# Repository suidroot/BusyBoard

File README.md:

# BusyBoard

The Busy board is a board designed for experimetning with various Microcontroller Dev boards. It is there to give you LEDs to make blink, various, buttons, switches and knobs to learn and test code against. The choice in components is based around what parts I have on hand and what is easily available in most beginers kits.

_Currently it has the following features_
* 4x LEDs
* 4x push buttons
* 8x DIP switches
* 1x Rotary Encorder
* 1x variable potentiometer
* Optional Pull up resistors (enabled by switch)
* Small power distribution array of Pins

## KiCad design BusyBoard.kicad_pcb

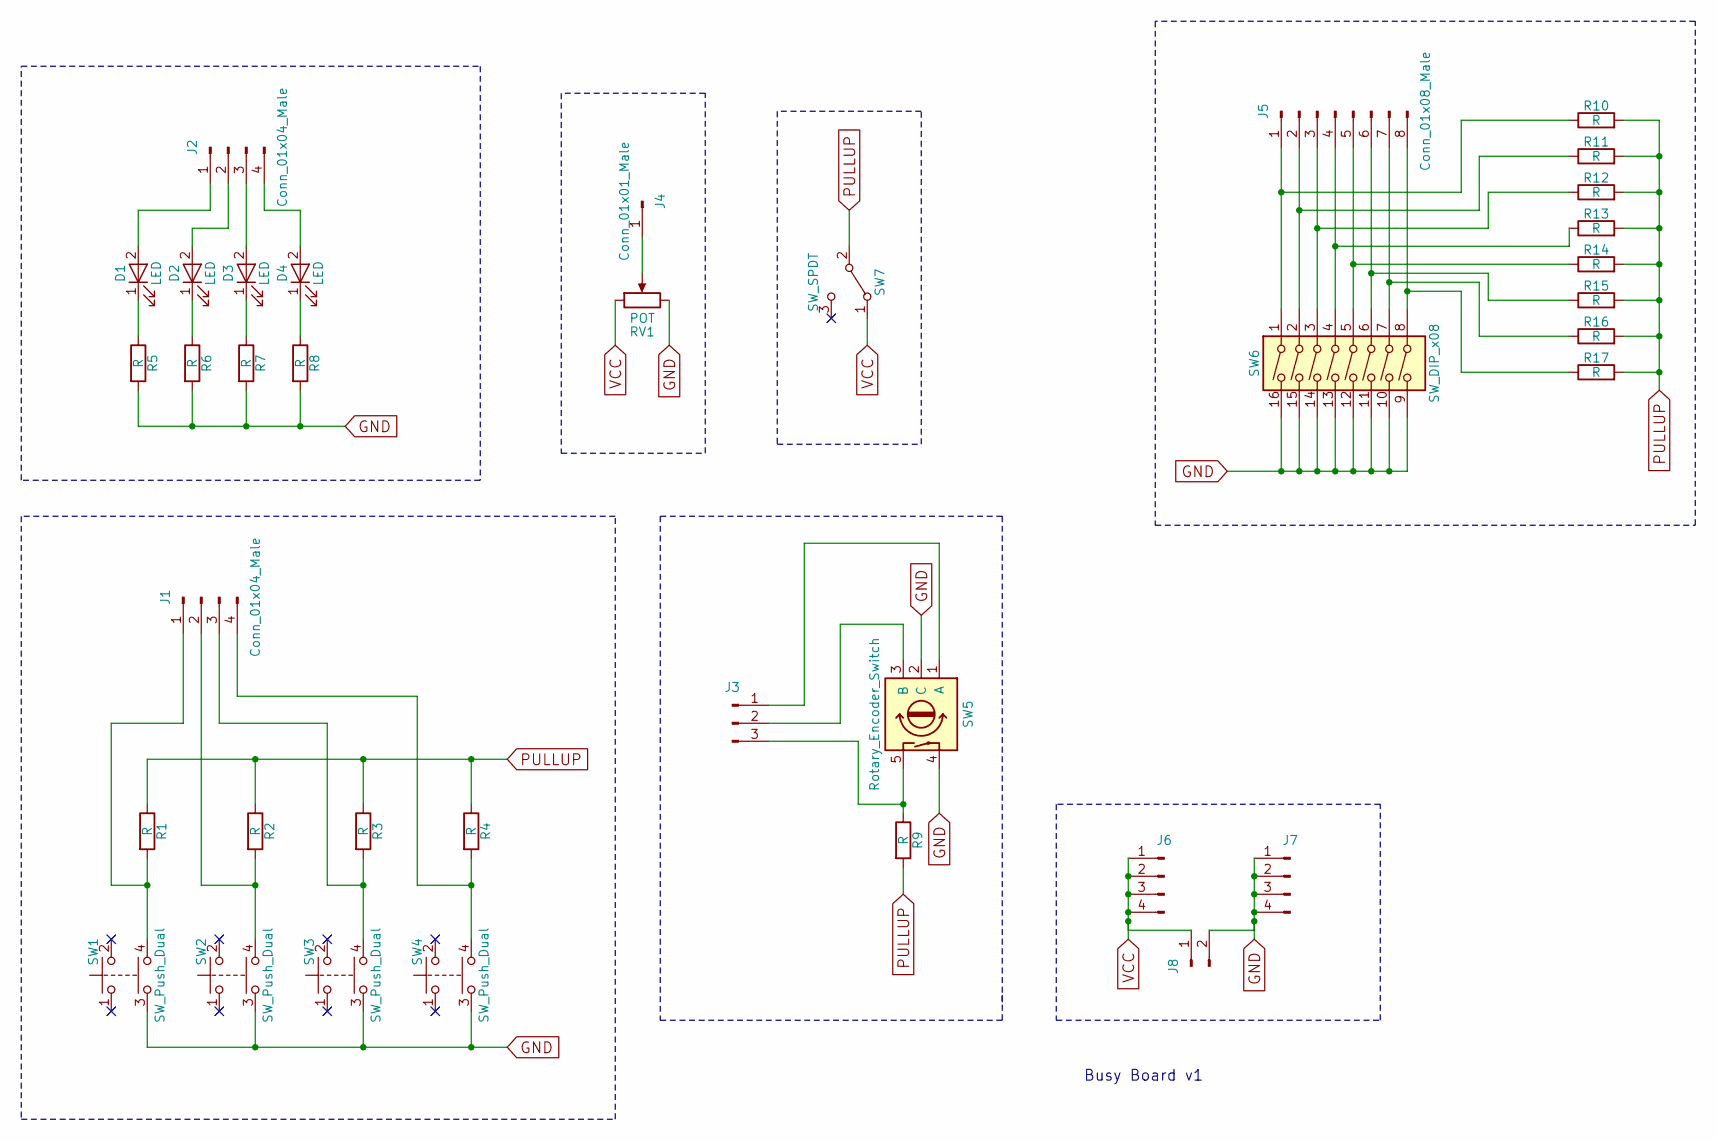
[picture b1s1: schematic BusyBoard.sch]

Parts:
D1, D2, D3, D4: LED; LED-5MM
J1, J2, J6, J7: Conn_01x04_Male; Pin_Header_Straight_1x04_Pitch2.54mm
J3: Conn_01x03_Male; Pin_Header_Straight_1x03_Pitch2.54mm
J4: Conn_01x01_Male; Pin_Header_Straight_1x01_Pitch2.54mm
J5: Conn_01x08_Male; Pin_Header_Straight_1x08_Pitch2.54mm
J8: Conn_01x02_Male; Pin_Header_Straight_1x02_Pitch2.54mm
R1, R2, R3, R4, R5, R6, R7, R8, R9, R10, R11, R12, R13, R14, R15, R16, R17: R; R_Axial_DIN0207_L6.3mm_D2.5mm_P10.16mm_Horizontal
RV1: POT; TSR-3386U_THT_306E_U_103
SW1, SW2, SW3, SW4: SW_Push_Dual; Button_Tactile_DPDT_4
SW5: Rotary_Encoder_Switch; Ben_Tactile_SPST
SW6: SW_DIP_x08; SW_DIP_x8_Slide
SW7: SW_SPDT; SW_Micro_SPST

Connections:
GND: J7.1, J7.2, J7.3, J7.4, J8.2, R5.2, R6.2, R7.2, R8.2, RV1.3, SW1.3, SW2.3, SW3.3, SW4.3, SW5.2 (C), SW5.4, SW6.9, SW6.10, SW6.11, SW6.12, SW6.13, SW6.14, SW6.15, SW6.16
unnamed: D1.1 (K), R5.1
unnamed: D1.2 (A), J2.1
unnamed: D2.1 (K), R6.1
unnamed: D2.2 (A), J2.2
unnamed: D3.1 (K), R7.1
unnamed: D3.2 (A), J2.3
unnamed: D4.1 (K), R8.1
unnamed: D4.2 (A), J2.4
unnamed: J1.1, R1.2, SW1.4
unnamed: J1.2, R2.2, SW2.4
unnamed: J1.3, R3.2, SW3.4
unnamed: J1.4, R4.2, SW4.4
unnamed: J3.1, SW5.1 (A)
unnamed: J3.2, SW5.3 (B)
unnamed: J3.3, R9.1, SW5.5
unnamed: J4.1, RV1.2
unnamed: J5.1, R10.1, SW6.1
unnamed: J5.2, R11.1, SW6.2
unnamed: J5.3, R12.1, SW6.3
unnamed: J5.4, R13.1, SW6.4
unnamed: J5.5, R14.1, SW6.5
unnamed: J5.6, R15.1, SW6.6
unnamed: J5.7, R16.1, SW6.7
unnamed: J5.8, R17.1, SW6.8
PULLUP: R1.1, R2.1, R3.1, R4.1, R9.2, R10.2, R11.2, R12.2, R13.2, R14.2, R15.2, R16.2, R17.2, SW7.2 (B)
VCC: J6.1, J6.2, J6.3, J6.4, J8.1, RV1.1, SW7.1 (A)

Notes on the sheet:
Busy Board v1

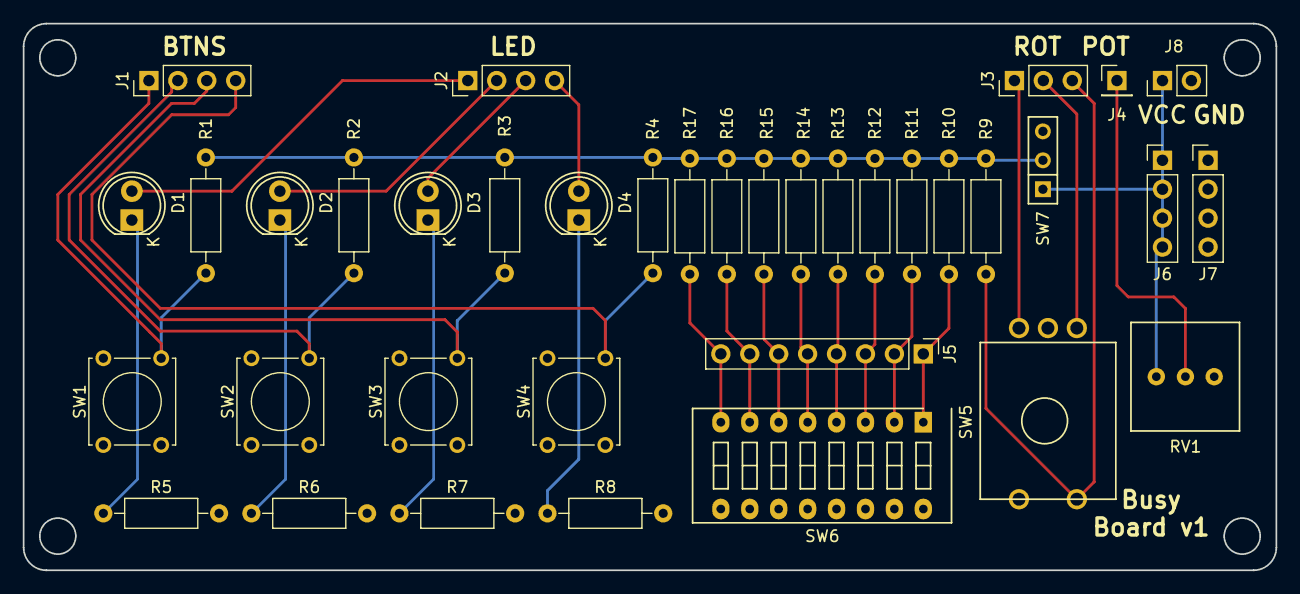
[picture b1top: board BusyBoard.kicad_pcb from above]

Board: 2 copper layers, 110.0 x 48.0 mm, 37 parts (0 on the bottom side), 27 nets.

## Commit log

2018-02-10 Adding Gitignore
2018-02-11 Board Version v1
2018-02-26 update gitignore
2018-02-26 Adding Board Test Suite
2018-02-26 Remove compiled data
